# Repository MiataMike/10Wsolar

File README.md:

# 10Wsolar
This project is a solar power converter for charging the 12V battery in my truck with a 10W solar panel I got from amazon. 
## MPPT control
Solar panels deliver different currents at different voltages, in the specs below we can see it's 0A @ 21V and .57A @ 17.5V.
 The power of the first is 0W and the second is 10W, so we can get more power from our panel if we operate at the optimal voltage.
 The microcontroller will vary the duty cycle of the buck converter, lowering the voltage of the panel from between open circuit voltage and the battery's voltage.
 Additionally, I don't want to overcharge the battery (It's currently directly connected and who knows what rate it's working at) so I'll add some control logic to trickle charge the battery.
 Since I'm a data geek, I've added an SD card so I can monitor the panel's performance over time, and the truck's (hopefully full) state of charge.
 # Parts
 
 ## Voltage sensing
 The voltage sensing is reading the panel's voltage and the battery's voltage. The panel voltage is used in the control loop to calculate the power we're pulling from the panel. The battery voltage is measured to check state of charge.
 I've used high value resistors because this current draw is constant, even at night. The filtering is agressive so I'll need to slow down my control loop and watch out for oscillation.

 ## CPU
 I've wanted to get my feet wet with ARM processors after taking a class on them in college. This processor has a small form factor and low power to boost efficiency.
 
## Buck converter
Thanks TI for making the buck converter component datasheet! I've chosen values from the panel specs below, but added a much larger inductor in case my frequency needs to go down, or I want to convert much smaller currents
I've added a backup diode in case the syncronous switching doesn't work out. 
 
## current sensing
TI also makes a great chip for monitoring the voltage across a shunt. Doing this with a single ended ADC would be a pain, and it comes with built in filtering and gain. 

## 3.3V converter
Thanks Collin Winans, I'm using his design for a 3.3V buck converter to supply power to the circuit. Most of the symbols in this design are his too.
This should be a very efficeint option since we're stepping down all the way from 12V, which would be a lot of energy to burn in a linear regulator.

## MPPT algorithm
At first, I may just close the top switch and collect data on what the panel does when it's connected directly. This would give me a baseline
From there, I would write code that calculates and optimizes the power coming from the panel. 
The hill climbing algorithm that changes direction every time it detects a drop in power should do nicely. 
Some other features I'd like to add are:
- sleeping at night
- characterizing the panel (V vs A)
- voltage cutoff and derating based on battery voltage
- bitcoin mining to prevent overcharge (not on a Cortex-F0, but still)

## panel specs
- 21V open circuit
- 17.5V @peak power
- .57A 	@peak power
- stylish aluminum frame

# Routing considerations

## Current carrying
I'm designing this around a 1A nominal current, which is more than the 10W panel should put out on the 12V bus. Using a trace width calculator w/ 10C rise @ 1oz/ft^2, I get 11mil traces minimum. Lower trace resistance decreases losses, so this is a minimum

## Overall layout
when designing power electronics, it's important to imagine the current path and ground returns. Can you tell which way I routed it?

## Coil placement
 Big Bob is on the top, a horizontally mounted toroidal coil. On the bottom there's a bobbin wound inductor for the 5V supply.
 The direction of the magnetic field around the bobbin creates a toroid whose axis is normal to the board while the toroid creates a field in a circle along the plane of the board.
 Having these fields at 90 degrees should minimize coupling.

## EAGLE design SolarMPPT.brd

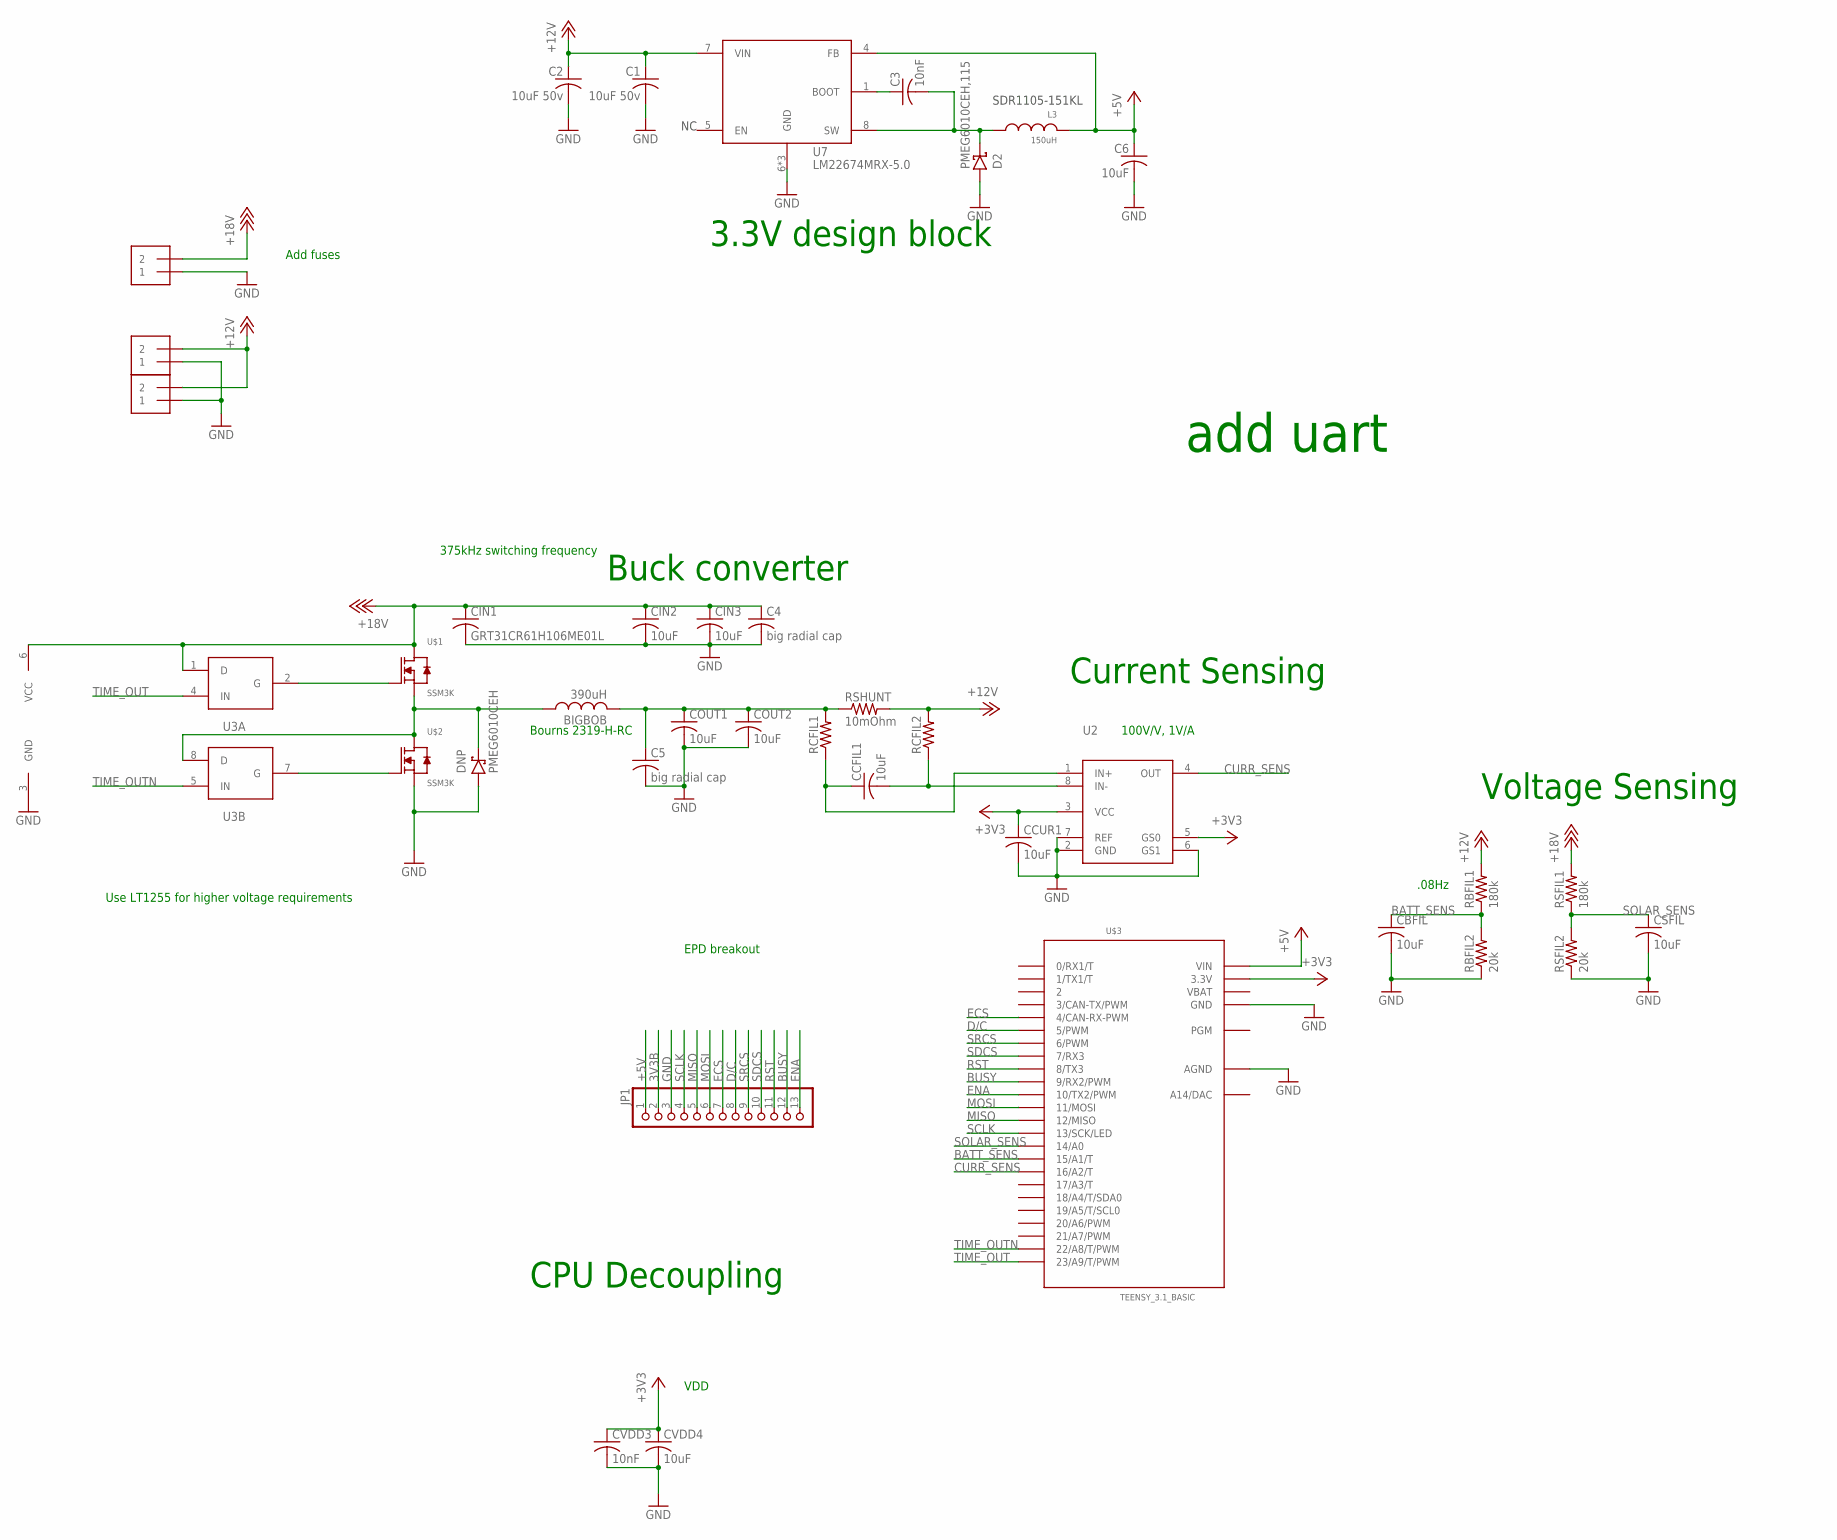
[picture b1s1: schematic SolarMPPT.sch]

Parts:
BIGBOB: 390uH; TJ6-U2
C1: 10uF 50v; C0805; PARTNO UMK212BJ105KG-T
C2: 10uF 50v; C1206; PARTNO GRM31CR71H475KA12L
C3: 10nF; C0805; PARTNO GRM216R71H103KA01D
C4, C5: big radial cap; C050-024X044
C6: 10uF; C0805; PARTNO GRM21BR61E106KA73L
CBFIL: 10uF; C0805
CCFIL1: 10uF; C0805
CCUR1: 10uF; C0805
CIN1: GRT31CR61H106ME01L; C1206
CIN2, CIN3: 10uF; C1206
COUT1, COUT2: 10uF; C1206
CSFIL: 10uF; C0805
CVDD3: 10nF; C0805
CVDD4: 10uF; C0805
D2: PMEG6010CEH,115; SOD-123; PARTNO PMEG6010CEH115
DNP: PMEG6010CEH; SOD-123
J2, J3, J6: 1X2-3.5MM
JP1: PINHD-1X13; 1X13
L3: 150uH; SDR1105; PARTNO SDR1105-151KL
RBFIL1: 180k; R0805
RBFIL2: 20k; R0805
RCFIL1, RCFIL2: R-US_R0805; R0805
RSFIL1: 180k; R0805
RSFIL2: 20k; R0805
RSHUNT: 10mOhm; R1206
U2: INA225VSSOP; VSSOP-8
U3: LTC1155; LT-SOL8
U7: LM22674MRX-5.0; SOIC-8-POWERPAD; PARTNO LM22674MRX-5.0/NOPB
U$1, U$2: SSM3K; SOT-23-MOSFET
U$3: TEENSY_3.1_BASIC

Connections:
3V3B: JP1.2
+3V3: CCUR1.1, CVDD3.1, CVDD4.1, U2.3 (VCC), U2.5 (GS0), U$3.3.3V, U$3.3.3V1 (3.3V)
+5V: C6.1, JP1.1, L3.P$1, U7.4 (FB), U$3.VIN
+12V: C1.1, C2.1, J2.2, J3.2, RBFIL1.2, RCFIL2.2, RSHUNT.2, U7.7 (VIN)
+18V: C4.1, CIN1.1, CIN2.1, CIN3.1, J6.2, RSFIL1.2, U3.1 (D), U3.6 (VCC), U$1.D
BATT_SENS: CBFIL.1, RBFIL1.1, RBFIL2.2, U$3.15/A1 (15/A1/T)
BOOT_5V2: C3.1, U7.1 (BOOT)
BUSY: JP1.12, U$3.9 (9/RX2/PWM)
CURR_SENS: U2.4 (OUT), U$3.16/A2 (16/A2/T)
D/C: JP1.8, U$3.5 (5/PWM)
ECS: JP1.7, U$3.4 (4/CAN-RX-PWM)
ENA: JP1.13, U$3.10 (10/TX2/PWM)
GND: C1.2, C2.2, C4.2, C5.2, C6.2, CBFIL.2, CCUR1.2, CIN1.2, CIN2.2, CIN3.2, COUT1.2, COUT2.2, CSFIL.2, CVDD3.2, CVDD4.2, D2.A, DNP.A, J2.1, J3.1, J6.1, JP1.3, RBFIL2.1, RSFIL2.1, U2.2 (GND), U2.6 (GS1), U2.7 (REF), U3.3 (GND), U7.6 (GND), U7.PAD (GND), U7.PAD1 (GND), U$2.S, U$3.AGND, U$3.GND, U$3.GND1 (GND)
MISO: JP1.5, U$3.12 (12/MISO)
MOSI: JP1.6, U$3.11 (11/MOSI)
unnamed: U3.2 (G), U$1.G
unnamed: CCFIL1.2, RCFIL2.1, U2.8 (IN-)
unnamed: CCFIL1.1, RCFIL1.1, U2.1 (IN+)
unnamed: BIGBOB.1, DNP.K, U3.8 (D), U$1.S, U$2.D
unnamed: U3.7 (G), U$2.G
unnamed: BIGBOB.2, C5.1, COUT1.1, COUT2.1, RCFIL1.2, RSHUNT.1
RST: JP1.11, U$3.8 (8/TX3)
SCLK: JP1.4, U$3.13 (13/SCK/LED)
SDCS: JP1.10, U$3.7 (7/RX3)
SOLAR_SENS: CSFIL.1, RSFIL1.1, RSFIL2.2, U$3.14/A0
SRCS: JP1.9, U$3.6 (6/PWM)
SW_5V2: C3.2, D2.K, L3.P$2, U7.8 (SW)
TIME_OUT: U3.4 (IN), U$3.23/A9 (23/A9/T/PWM)
TIME_OUTN: U3.5 (IN), U$3.22/A8 (22/A8/T/PWM)
VBAT: U$3.VBAT

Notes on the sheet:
VDD
.08Hz
100V/V, 1V/A
375kHz switching frequency
Use LT1255 for higher voltage requirements
Bourns 2319-H-RC
Voltage Sensing
Current Sensing
CPU Decoupling
3.3V design block
Buck converter
SDR1105-151KL
Add fuses
add uart
EPD breakout

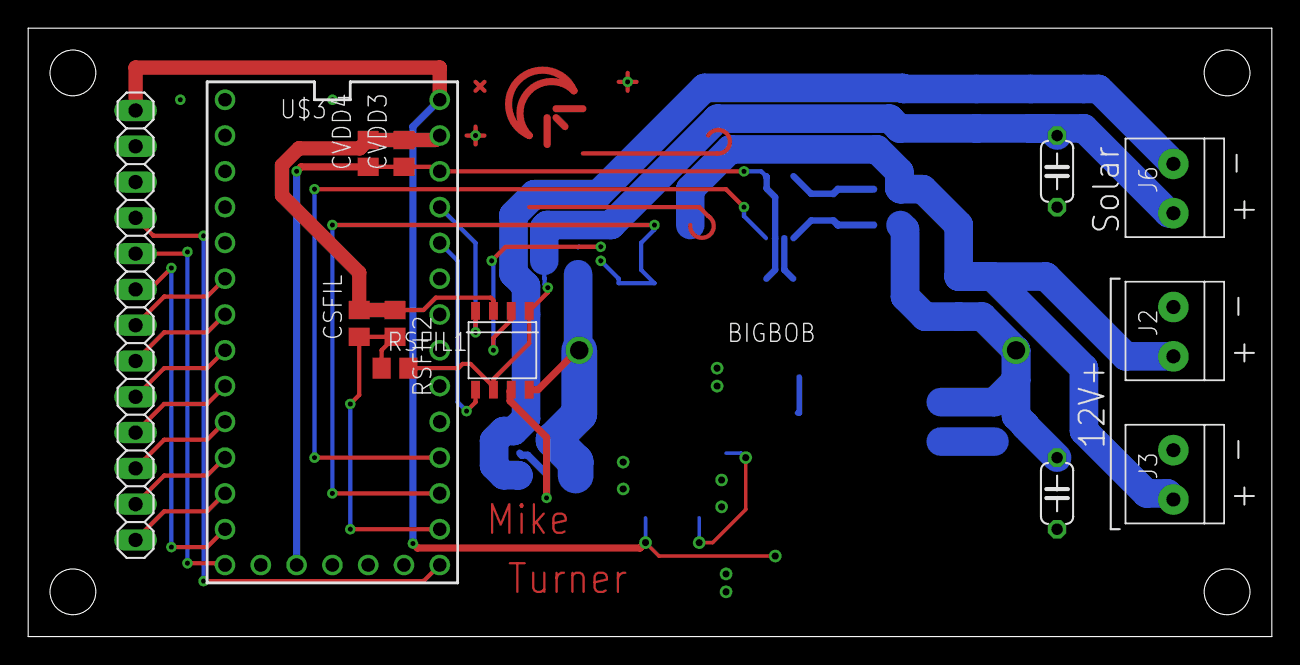
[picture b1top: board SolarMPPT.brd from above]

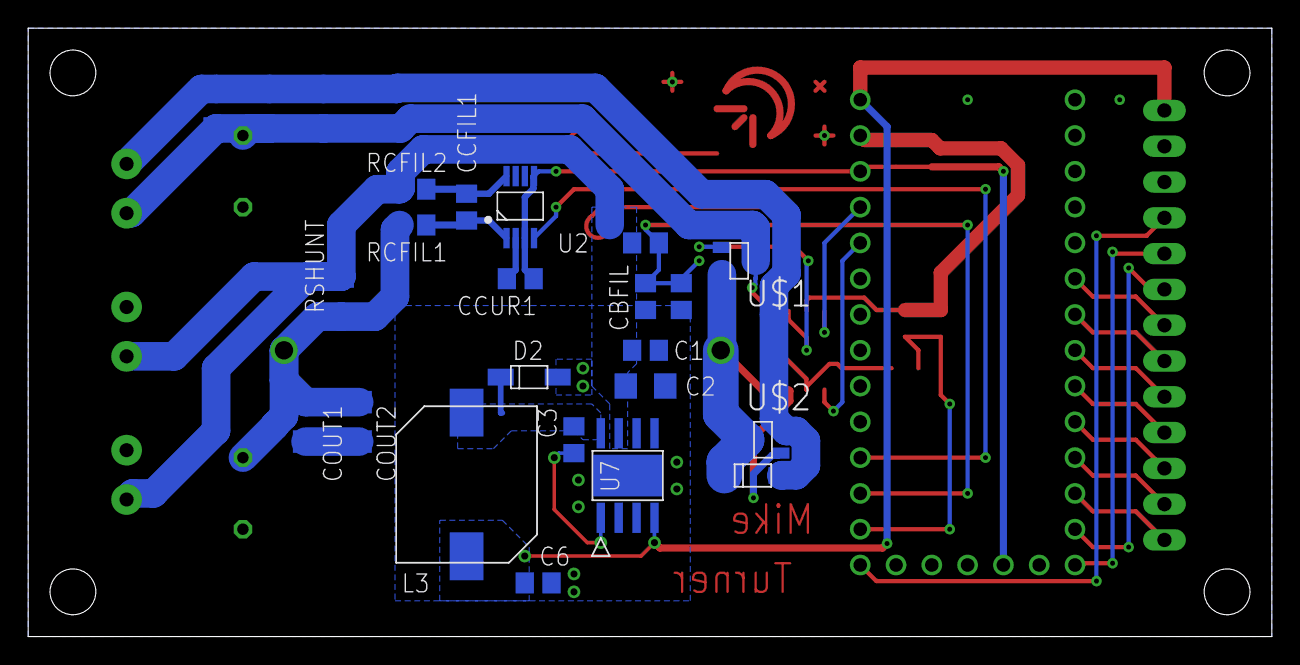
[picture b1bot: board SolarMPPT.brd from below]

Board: 2 copper layers, 88.3 x 43.2 mm, 38 parts (24 on the bottom side), 28 nets.

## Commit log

2020-05-30 Adding eagle schematic and Buck calculator
2020-05-30 Added LT1255 gate driver and MOSFETs
2020-05-30 finished Buck component selection
2020-05-30 Added decoupling caps, cleaned up schematic, ready for review
2020-05-30 Updated 'documentation' and spreadsheet
2020-05-30 added spaces to fix markup
2020-05-31 created brd file and sorted into categories
2020-05-31 placed components in rough location. Might remap ADC pins for routing
2020-05-31 Did power routing and added terminals
2020-06-07 added teensy, removed SD
2020-06-07 removed 3.3v regulator (using teensy onboard)
2020-06-07 routed!
2020-06-09 added mounting holes, art, and generally cleaned up before ordering!
2020-06-09 Went back and forth with osh getting it right, this version was ORDERED
2020-06-13 Created digikey cart, updated schematic with components
2020-06-30 Created the foundation for a cool retro display
2020-07-01 Changed the look of the display, added Terminal
2020-07-03 adding functions, moving to graph class
2020-07-03 Pushing files because I'm going outside!
2020-07-04 Lots of improvements! SD card, good graphing, real readouts oh my
2020-07-09 Added datalog of 24 hours!
2020-07-11 I suspect this is the fix
2020-07-11 This is what I intended
2020-07-11 Added linear correction for reading
2020-07-11 Fixed a typo
2020-07-11 adding picture
2020-08-16 added hillclimbing optimization algo
2020-09-05 Moved to separate loops for ctrl and display so ctrl loop reacts faster
2021-06-06 added datalogs
